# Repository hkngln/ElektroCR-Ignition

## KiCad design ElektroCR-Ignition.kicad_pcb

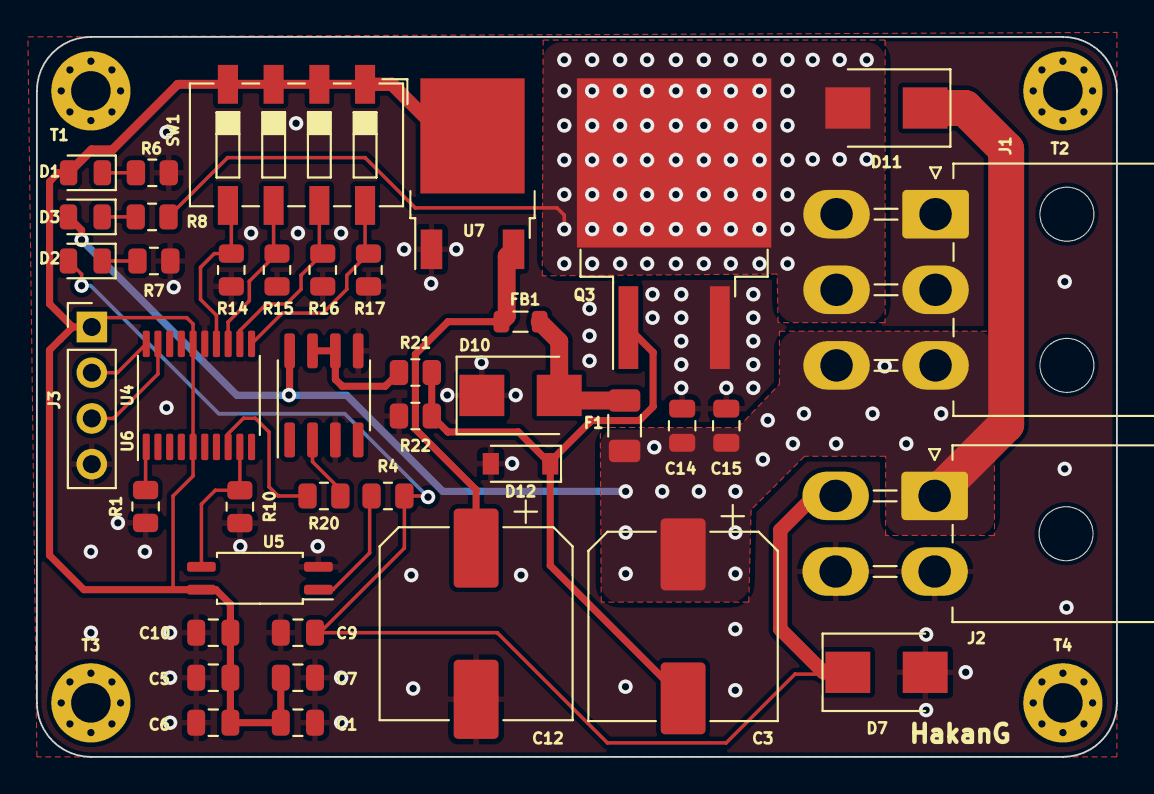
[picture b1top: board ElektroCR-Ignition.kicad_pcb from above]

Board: 2 copper layers, 60.0 x 40.0 mm, 45 parts (0 on the bottom side), 23 nets.

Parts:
C1, C14, C15: 100uF; C_0805_2012Metric
C3: 470uF; CP_Elec_10x10
C5, C6, C9, C10: 100nF; C_0805_2012Metric
C7: 47nF; C_0805_2012Metric
C12: 1000uF; CP_Elec_10x10.5
D1, D2, D3: LED; LED_0805_2012Metric
D7, D10: 16,7V; D_SMB
D11: SMB 2A; D_SMB
D12: 12V; D_SOD-123
F1: Fuse; Fuse_1206_3216Metric
FB1: 100R; L_0805_2012Metric
J1: POWER; Molex_Mini-Fit_Jr_5569-06A2_2x03_P4.20mm_Horizontal
J2: HALL-SENS; Molex_Mini-Fit_Jr_5569-04A2_2x02_P4.20mm_Horizontal
J3: Conn_01x04; PinHeader_1x04_P2.54mm_Vertical
Q3: BUK9640; TO-263-2
R1: 4K7; R_0805_2012Metric
R4, R6, R7, R8: 330; R_0805_2012Metric
R10: 1K; R_0805_2012Metric
R14, R15, R16, R17, R22: 10K; R_0805_2012Metric
R20: 220; R_0805_2012Metric
R21: 33; R_0805_2012Metric
SW1: SW_DIP_x04; SW_DIP_SPSTx04_Slide_6.7x11.72mm_W6.73mm_P2.54mm_LowProfile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
T1, T2, T3, T4: MountingHole_2.2mm_M2_Pad_Via
U4: STM32L031F4Px; TSSOP-20_4.4x6.5mm_P0.65mm
U5: TLP291; SOIC-4_4.55x2.6mm_P1.27mm
U6: TLP250; SOIC-8_3.9x4.9mm_P1.27mm
U7: LM1117-3.3; TO-252-2

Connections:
+3V3: C1.1, C5.1, C6.1, C7.1, C10.1, D1.2 (A), J3.1, SW1.1, SW1.2, SW1.3, SW1.4, U4.5 (VDDA), U4.16 (VDD), U5.4, U7.2 (VO)
/A: R14.1, SW1.5, U4.14 (PB1)
/B: R15.1, SW1.6, U4.13 (PA7)
/C: R16.1, SW1.7, U4.12 (PA6)
/D: R17.1, SW1.8, U4.11 (PA5)
/MCU_IGN_OUT: R20.1, U4.8 (PA2)
/MCU_PULSE: R10.1, U4.9 (PA3), U5.3
/SWDCLK: J3.2, U4.20 (PA14)
/SWDIO: J3.3, U4.19 (PA13)
GND: C1.2, C5.2, C6.2, C7.2, C9.2, C10.2, C12.2, C14.2, C15.2, D7.2 (A2), D10.1 (A1), D12.2 (A), J1.1, J1.2, J2.2, J2.4, J3.4, Q3.3 (S), R1.1, R6.1, R7.1, R10.2, R14.2, R15.2, R16.2, R17.2, R22.2, U4.15 (VSS), U5.2, U6.3 (C), U6.5 (VEE), U7.1 (GND)
IGN_OUT2: D11.2 (A), J1.4, J1.5, Q3.2 (D), R8.1
unnamed: C3.2, D12.1 (K), Q3.1 (G), R21.2, R22.1
unnamed: C12.1, FB1.2, U7.3 (VI)
unnamed: D1.1 (K), R6.2
unnamed: D2.1 (K), R7.2
unnamed: D3.1 (K), R8.2
unnamed: D10.2 (A2), F1.2, FB1.1
unnamed: R1.2, U4.1 (BOOT0)
unnamed: R4.1, U5.1
unnamed: R20.2, U6.2 (A)
unnamed: R21.1, U6.6 (VO), U6.7 (VO)
PULSE: C9.1, D2.2 (A), D7.1 (A1), J2.3, R4.2
Vbat: C3.1, C14.1, C15.1, D3.2 (A), D11.1 (K), F1.1, J1.3, J1.6, J2.1, U6.8 (VCC)

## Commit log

2021-06-26 İgnition circuit
2021-06-26 Kicad versiyon güncellendi
2021-06-28 ignore
